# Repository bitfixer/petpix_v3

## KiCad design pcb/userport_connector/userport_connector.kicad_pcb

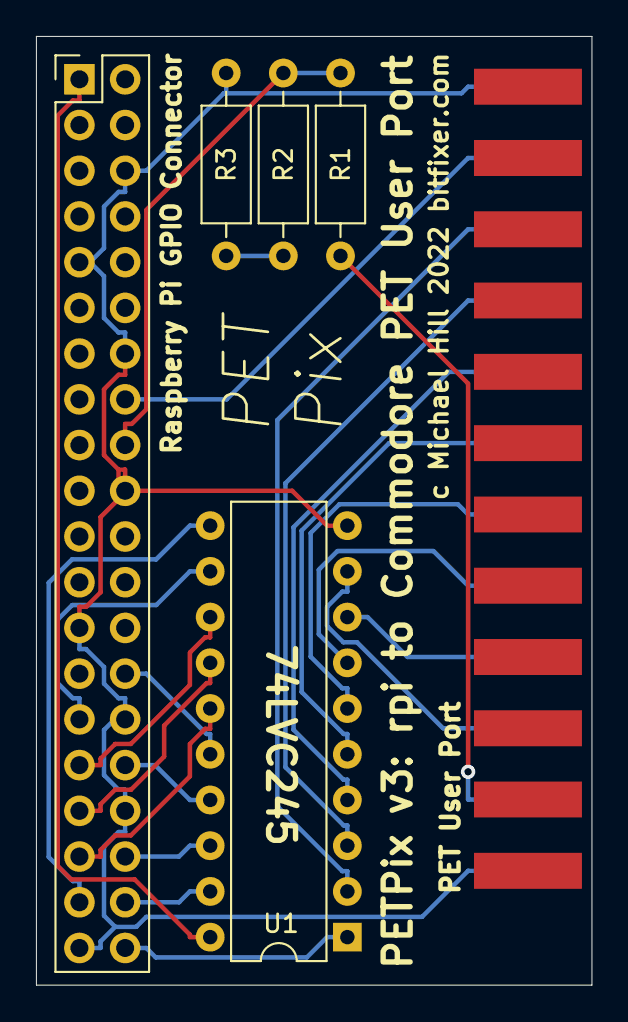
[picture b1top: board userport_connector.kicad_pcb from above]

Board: 2 copper layers, 30.9 x 52.7 mm, 6 parts (0 on the bottom side), 24 nets.

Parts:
J1: PET User Port; 2x12_Card_Edge
J2: Raspberry_Pi_2_3; PinHeader_2x20_P2.54mm_Vertical
R1, R2, R3: 1K; R_Axial_DIN0207_L6.3mm_D2.5mm_P10.16mm_Horizontal
U1: 74LVC245; DIP-20_W7.62mm

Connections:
+3V3: J2.1, U1.20
BCB2: J2.18, R1.2, R2.1
CA1: J1.14, J2.16
CB2: J1.23, R1.1
D0: J2.36, U1.18
D1: J2.32, U1.17
D2: J2.28, U1.16
D3: J2.35, U1.15
D4: J2.33, U1.14
D5: J2.31, U1.13
D6: J2.29, U1.12
D7: J2.37, U1.11
DIR: J2.40, U1.1
GND: J1.13, J1.24, J2.6, J2.9, J2.14, J2.20, J2.25, J2.30, J2.34, J2.39, R3.2, U1.10
unnamed: R2.2, R3.1
OUTPUT_ENABLE_BAR: J2.38, U1.19
PB0: J1.15, U1.2
PB1: J1.16, U1.3
PB2: J1.17, U1.4
PB3: J1.18, U1.5
PB4: J1.19, U1.6
PB5: J1.20, U1.7
PB6: J1.21, U1.8
PB7: J1.22, U1.9

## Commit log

2022-07-15 source added
2022-07-16 cleanup
2022-07-16 WIP 1
2022-07-16 pet dispay client
2022-07-16 add delay option back
2022-07-16 faster FPS
2022-07-16 timing
2022-07-17 faster client
2022-07-17 added petscii conversion
2022-07-17 stream fixes
2022-07-18 experiment with simple glyph matching
2022-07-19 sorting glyphs for simple search
2022-07-19 search range
2022-07-19 more optimization,quadrants
2022-07-19 multithreaded
2022-07-19 thread param
2022-07-19 added brightness range
2022-07-19 fix quad check
2022-07-19 param for output image
2022-07-19 more tweaks
2022-07-19 quad mean divisor
2022-07-19 use sixteenths for filtering
2022-07-20 sort error
2022-07-20 Revert "sort error"
    This reverts commit ae3aa4cce9a0c7f1c0d7cb3ede60317f3d866909.
2022-07-20 bucket sorting
2022-07-20 more cleanup
2022-07-20 add scripts
2022-07-20 add option to exclude letters
2022-07-20 userport connector pcb
2022-07-21 image upload from html
2022-07-21 phone streaming partially working
2022-07-23 add startup args to petpix
2022-07-23 use grayscale value in detection
2022-07-24 switching works
2022-07-24 scaled video to window width
2022-07-25 rgb sliders
2022-07-25 fixed sliders
2022-07-26 more stream options
2022-07-27 timed sender
2022-07-28 generate tests script
2022-07-30 added 80 column support
2022-08-02 changed gpio pins
2022-08-02 fixed check for q key to exit
2022-08-02 fixed board problem
2022-08-02 fixed stream targets
2022-08-03 support 80 columns
2022-08-04 skip late frames
2022-08-04 fix path on testupload.php
2022-08-05 removed non local references
2022-08-05 redirect to https
2022-08-05 change 80 column client to only send 2000 characters
2022-08-06 add file conversion program
2022-08-15 disable speaker in 80 column client
2022-08-16 added interleaving experiment
2022-08-17 setup script
2022-08-17 change submodule links
2022-08-17 more setup script
2022-08-17 more config files
2022-08-17 more setup
2022-08-18 log output from petpix
2022-08-19 file uploading
2022-08-27 add loop version of 40 col client
2022-09-02 WIP petpixPlayer
2022-09-02 WIP petpix player
2022-09-02 playlist editor
2022-09-02 upload file with javascript
2022-09-02 remove video file after upload
2022-09-02 start up petpixPlayer at launch
2022-09-04 playlist writing
2022-09-04 fix control byte file
2022-09-04 change setup
2022-09-05 find prefix for mov files
2022-09-06 remove dependence on stream script
2022-09-07 added php.ini to setup
2022-09-07 updated setup
2022-09-07 add more controls
2022-09-07 support progress
2022-09-07 use temp folder for progress
2022-09-07 simplify setup
2022-10-17 refactor for video conversion
2023-08-02 fixes for install and startup scripts
2023-08-02 fix for 80 column capture mode
2024-08-01 added test mode
2025-07-31 added simplified pet byte sender
2025-07-31 added timed sender over udp
2025-07-31 updated udp sender
2025-07-31 trying tcp
2025-07-31 fix for front camera
2025-08-01 web fixes
2025-08-01 fix canvas size
